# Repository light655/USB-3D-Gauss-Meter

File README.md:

# USB 3D-Gauss Meter

This project is a USB 3D-Gauss Meter based on Texas Instrument's TMAG5170 Hall Sensor.
The Gauss Meter is powered by an STM32, which sends the measured data through USB.
A Python GUI client is provided to show the measured results.

## Files
- document: Images used in this README file.
- firmware: Source code of the firmware for the STM32.
- hardware: Kicad project of the PCB design.
- python-client: The Python GUI client. Please visit [my website](https://light655.github.io/Product/gauss_meter.html) for instructions.
- shell: The 3D-printed shell model.

## Python GUI client
Please visit [my website](https://light655.github.io/Product/gauss_meter.html) for instructions.

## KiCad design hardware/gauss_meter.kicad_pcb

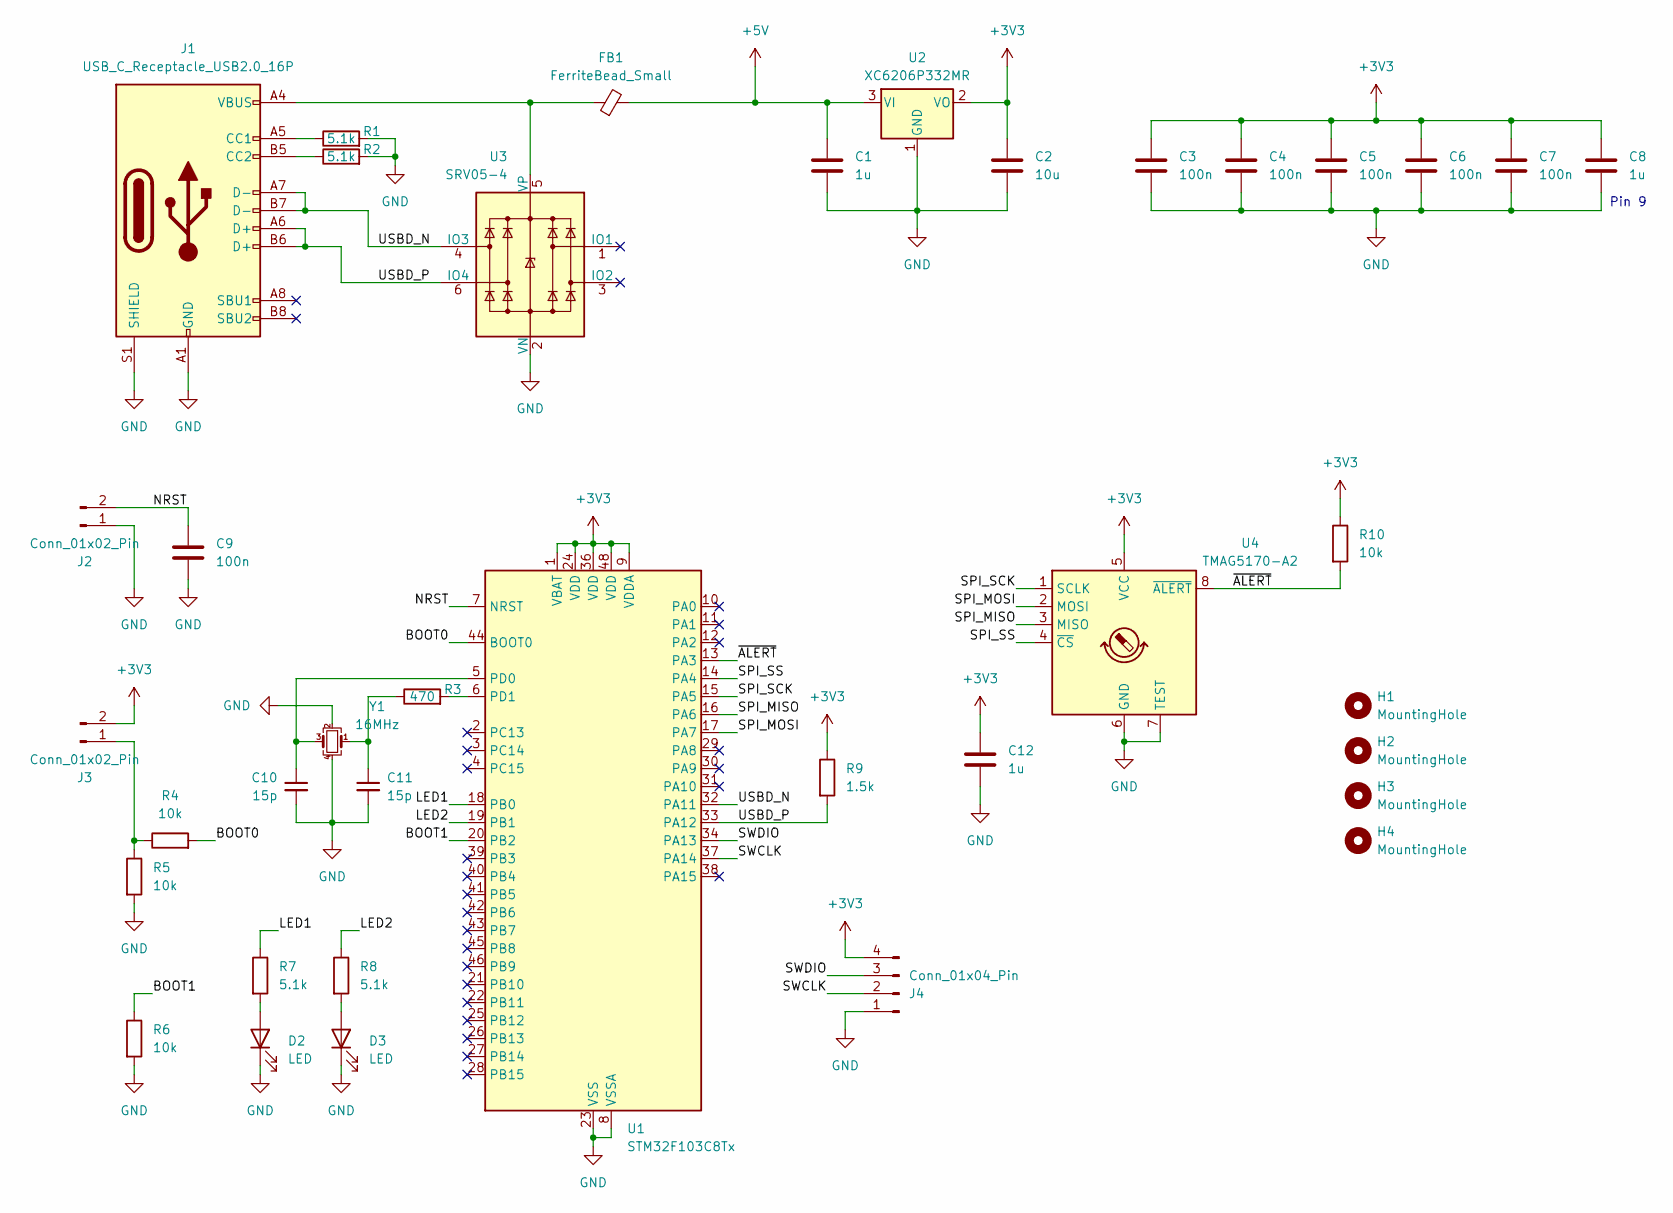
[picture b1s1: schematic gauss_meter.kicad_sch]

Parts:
C1, C8, C12: 1u; C_0603_1608Metric_Pad1.08x0.95mm_HandSolder; LCSC C15849
C2: 10u; C_0603_1608Metric_Pad1.08x0.95mm_HandSolder; LCSC C96446
C3, C4, C5, C6, C7, C9: 100n; C_0402_1005Metric_Pad0.74x0.62mm_HandSolder; LCSC C307331
C10, C11: 15p; C_0402_1005Metric_Pad0.74x0.62mm_HandSolder; LCSC C1548
D2: LED; LED_0805_2012Metric_Pad1.15x1.40mm_HandSolder; LCSC C2297
D3: LED; LED_0805_2012Metric_Pad1.15x1.40mm_HandSolder; LCSC C84256
FB1: FerriteBead_Small; L_0805_2012Metric_Pad1.15x1.40mm_HandSolder; LCSC C1015
H1, H2, H3, H4: MountingHole; MountingHole_3.2mm_M3
J1: USB_C_Receptacle_USB2.0_16P; USB_C_Receptacle_XKB_U262-16XN-4BVC11; LCSC C319148
J2, J3: Conn_01x02_Pin; PinHeader_1x02_P2.54mm_Vertical
J4: Conn_01x04_Pin; zigzag_pin_header_2.545mm_4p
R1, R2, R7, R8: 5.1k; R_0402_1005Metric_Pad0.72x0.64mm_HandSolder; LCSC C25905
R3: 470; R_0402_1005Metric_Pad0.72x0.64mm_HandSolder; LCSC C25117
R4, R5, R6, R10: 10k; R_0402_1005Metric_Pad0.72x0.64mm_HandSolder; LCSC C25744
R9: 1.5k; R_0402_1005Metric_Pad0.72x0.64mm_HandSolder; LCSC C25867
U1: STM32F103C8Tx; LQFP-48_7x7mm_P0.5mm; LCSC C8734
U2: XC6206P332MR; SOT-23-3; LCSC C5446
U3: SRV05-4; SOT-23-6; LCSC C85364
U4: TMAG5170-A2; VSSOP-8_3x3mm_P0.65mm; LCSC C3716101
Y1: 16MHz; Crystal_SMD_3225-4Pin_3.2x2.5mm; LCSC C13738

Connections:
+3V3: C2.1, C3.1, C4.1, C5.1, C6.1, C7.1, C8.1, C12.1, J3.2, J4.4, R9.1, R10.1, U1.1 (VBAT), U1.9 (VDDA), U1.24 (VDD), U1.36 (VDD), U1.48 (VDD), U2.2 (VO), U4.5 (VCC)
+5V: C1.1, FB1.2, U2.3 (VI)
/BOOT0: R4.2, U1.44 (BOOT0)
/BOOT1: R6.1, U1.20 (PB2)
/LED1: R7.1, U1.18 (PB0)
/LED2: R8.1, U1.19 (PB1)
/NRST: C9.1, J2.2, U1.7 (NRST)
/SPI_MISO: U1.16 (PA6), U4.3 (MISO)
/SPI_MOSI: U1.17 (PA7), U4.2 (MOSI)
/SPI_SCK: U1.15 (PA5), U4.1 (SCLK)
/SPI_SS: U1.14 (PA4), U4.4 (~CS)
/SWCLK: J4.2, U1.37 (PA14)
/SWDIO: J4.3, U1.34 (PA13)
/USBD_N: J1.A7 (D-), J1.B7 (D-), U1.32 (PA11), U3.4 (IO3)
/USBD_P: J1.A6 (D+), J1.B6 (D+), R9.2, U1.33 (PA12), U3.6 (IO4)
/~ALERT: R10.2, U1.13 (PA3), U4.8 (~ALERT)
GND: C1.2, C2.2, C3.2, C4.2, C5.2, C6.2, C7.2, C8.2, C9.2, C10.2, C11.2, C12.2, D2.1 (K), D3.1 (K), J1.A1 (GND), J1.A12 (GND), J1.B1 (GND), J1.B12 (GND), J1.S1 (SHIELD), J2.1, J4.1, R1.2, R2.2, R5.2, R6.2, U1.8 (VSSA), U1.23 (VSS), U1.35 (VSS), U1.47 (VSS), U2.1 (GND), U3.2 (VN), U4.6 (GND), U4.7 (TEST), Y1.2, Y1.4
unnamed: C11.1, R3.1, Y1.1
unnamed: D2.2 (A), R7.2
unnamed: D3.2 (A), R8.2
unnamed: J1.A5 (CC1), R1.1
unnamed: J1.B5 (CC2), R2.1
unnamed: J3.1, R4.1, R5.1
unnamed: C10.1, U1.5 (PD0), Y1.3
unnamed: R3.2, U1.6 (PD1)
unnamed: FB1.1, J1.A4 (VBUS), J1.A9 (VBUS), J1.B4 (VBUS), J1.B9 (VBUS), U3.5 (VP)

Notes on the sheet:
Pin 9

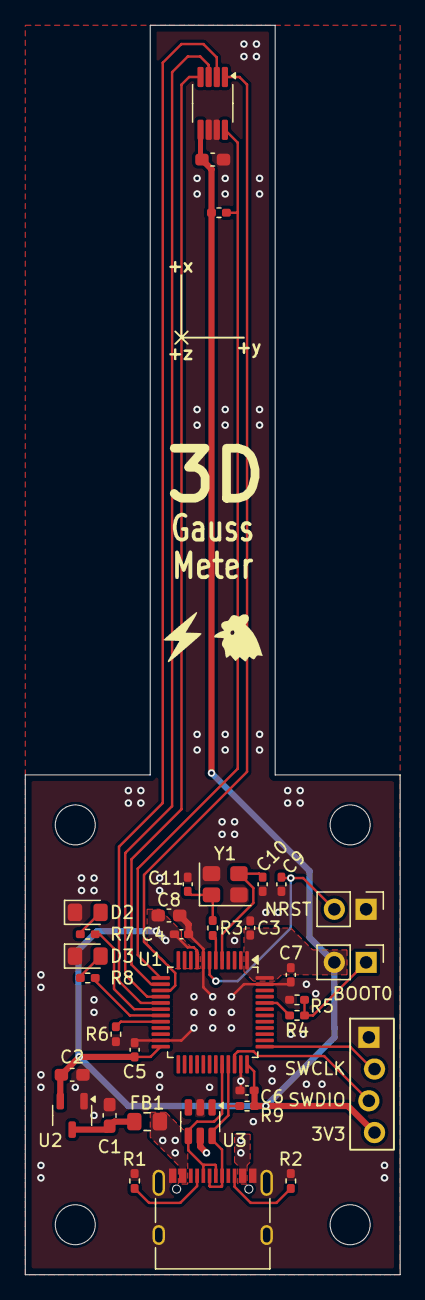
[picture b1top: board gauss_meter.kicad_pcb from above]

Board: 2 copper layers, 30.0 x 100.0 mm, 38 parts (0 on the bottom side), 26 nets.

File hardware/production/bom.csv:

Designator,Footprint,Quantity,Value,LCSC Part #
"C1, C12, C8",0603,3,1u,C15849
"C10, C11",0402,2,15p,C1548
C2,0603,1,10u,C96446
"C3, C4, C5, C6, C7, C9",0402,6,100n,C307331
D2,0805,1,LED,C2297
D3,0805,1,LED,C84256
FB1,0805,1,FerriteBead_Small,C1015
J1,USB_C_Receptacle_XKB_U262-16XN-4BVC11,1,USB_C_Receptacle_USB2.0_16P,C319148
"J2, J3",PinHeader_1x02_P2.54mm_Vertical,2,Conn_01x02_Pin,
J4,zigzag_pin_header_2.545mm_4p,1,Conn_01x04_Pin,
"R1, R2, R7, R8",0402,4,5.1k,C25905
"R10, R4, R5, R6",0402,4,10k,C25744
R3,0402,1,470,C25117
R9,0402,1,1.5k,C25867
U1,LQFP-48_7x7mm_P0.5mm,1,STM32F103C8Tx,C8734
U2,SOT-23-3,1,XC6206P332MR,C5446
U3,SOT-23-6,1,SRV05-4,C85364
U4,VSSOP-8_3x3mm_P0.65mm,1,TMAG5170-A2,C3716101
Y1,Crystal_SMD_3225-4Pin_3.2x2.5mm,1,16MHz,C13738

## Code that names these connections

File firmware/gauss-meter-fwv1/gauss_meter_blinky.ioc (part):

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Mcu.Name=STM32F103C(8-B)Tx
Mcu.Package=LQFP48
Mcu.UserName=STM32F103C8Tx
PA11.Mode=Device
PA11.Signal=USB_DM
PA12.Mode=Device
PA12.Signal=USB_DP
PA13.Mode=Serial_Wire
PA13.Signal=SYS_JTMS-SWDIO
PA14.Mode=Serial_Wire
PA14.Signal=SYS_JTCK-SWCLK
PA3.GPIOParameters=GPIO_ModeDefaultEXTI
PA3.GPIO_ModeDefaultEXTI=GPIO_MODE_IT_FALLING
PA3.Signal=GPXTI3
PA4.GPIOParameters=PinState
PA4.PinState=GPIO_PIN_SET
PA4.Signal=GPIO_Output
PA5.Mode=Full_Duplex_Master
PA5.Signal=SPI1_SCK
PA6.Mode=Full_Duplex_Master
PA6.Signal=SPI1_MISO
PA7.Mode=Full_Duplex_Master
PA7.Signal=SPI1_MOSI
PB0.Signal=GPIO_Output
PB1.Signal=GPIO_Output
PD0-OSC_IN.Mode=HSE-External-Oscillator
PD0-OSC_IN.Signal=RCC_OSC_IN
PD1-OSC_OUT.Mode=HSE-External-Oscillator
PD1-OSC_OUT.Signal=RCC_OSC_OUT
RCC.HSE_VALUE=16000000
RCC.SYSCLKFreq_VALUE=48000000
RCC.SYSCLKSource=RCC_SYSCLKSOURCE_PLLCLK
board=custom

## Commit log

2026-02-25 First commit.
2026-02-26 Added README.
2026-02-26 Added pictures to README.
2026-02-26 Created new python client with logging function.
2026-03-11 Added logging functions.
2026-03-12 LED lights up when measuring.
2026-03-12 Rearranged 3D printing model files.
2026-03-12 Added power status LED.
2026-03-25 Increased STM32 clock frequency to 72 MHz.
2026-03-25 Update sampling rate setting to actual values.
2026-03-25 Rearranged widgets.
2026-03-28 Improved Python client when not logging.
2026-03-28 Removed pause button.
2026-03-28 Set time to 0 when logging starts.
2026-03-28 Updated README.
2026-05-03 Updated .gitignore.
